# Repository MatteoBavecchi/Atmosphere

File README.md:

# Atmosphere

Air Quality Home Device

## Introduction

Atmosphere is the prototype of a device that detects some values of the surrounding air and let the the user know when it seems not to be livable.

All this is possible with the use of gas sensors, temperature sensors, a buzzer and a WiFi module which sends data collected to two servers.

The goal of the project is create a costomer product, in fact the Atmosphere ecosystem manages more than one user and catalogs the data sent by the various devices in a single database.

Any aspect has been studied to be as much as possible oriented towards an untrained user, and mobile friendly, that is viewable and configurable correctly from any mobile device.

The device is mainly composed by a customized electronic board and a plastic case manufactured with a 3D printer.<br>
Everything has been designed, designed, built and assembled by myself.

## PCB Board Design

I used the Atmega-328p_au for this project.
The PCB board has been made by OSH Park.

<a href="https://oshpark.com/shared_projects/vfo74W1z"></img></a>

## The webserver

Atmosphere communicates with the server http://atmosphere.96.lt and with the Thingspeak server, which can be reached from the IP address 184.106.153.149.
The dialogue with both servers is limited to a GET request on port 80, let's see how:

The syntax of the GET request to the Atmosphere server is as follows:

```
GET /data.php?mac=1&t=2&h=3&gpl=4&co2=5&co=6
```
1: MAC address that resides in the Atmosphere EEPROM.<br>
2: Temperature, expressed in degrees centigrade.<br>
3: Relative humidity, expressed as a percentage.<br>
4: Quantity of LPG in the air, expressed in ppm.<br>
5: Amount of CO2 present in the air, expressed in ppm.<br>
6: Amount of carbon monoxide in the air, expressed in ppm.<br>

The sintax for send data to the Thingspeak server is as follows:

```
GET   /update?key=1&field1=2&field2=3&field3=4&field4=5&field5=6
```
1: Thingspeak private key<br>
2: Temperature, in degrees centigrade.<br>
3: Relative humidity, expressed as a percentage.<br>
4: Quantity of LPG in the air, expressed in ppm.<br>
5: Amount of CO2 present in the air, expressed in ppm.<br>
6: Amount of carbon monoxide in the air, expressed in ppm.<br>

<br><br>
## How the device works

Atmosphere doesn't need expert users to be used, you just need to power on and it will automatically calibrate itself and begin to analyze the surrounding air, sending, every 30 seconds, the data on the internet.
Atmosphere has not any button or display that allows you to configure it. To make it connect to your home WiFi network, I created a smartphone app, which can communicate the login credentials to Atmosphere.

### First Startup
Atmosphere, when powered on, creates a WiFi network, this will be accessible for one minute.
We connect our smartphone to this network and start the "Atmosphere" App.
We have two fields to fill, the name of the network and the password, and under the "Send" button.
Below there's the MAC address of Atmosphere, this must be entered on the website during registration. By doing so, we associate our newly created account with our Atmosphere.
Let's go back to the smartphone and type the network credentials in the fields and press "Send".
Atmosphere will store them inside the EEPROM and connect to the desired network.

It can be powered with a micro usb cable, but even without this, it works for about an hour thanks to the internal battery.

<br><br>
## Database

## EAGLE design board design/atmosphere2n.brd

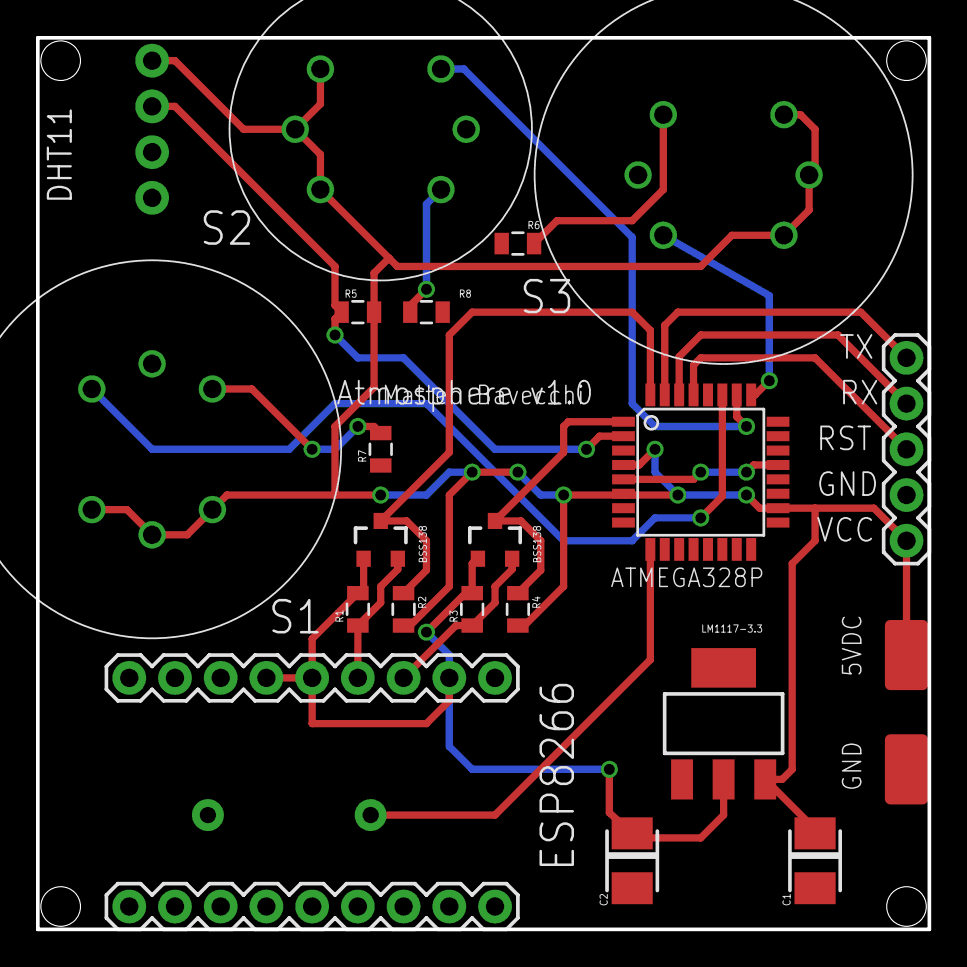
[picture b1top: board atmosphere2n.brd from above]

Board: 2 copper layers, 49.5 x 49.5 mm, 25 parts (0 on the bottom side), 18 nets.

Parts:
+: LUXEON-PAD
-: LUXEON-PAD
ATMEGA328P-AU: ATMEGA328; TQFP32-08
BSS138, BSS138-2: SOT23-3
BUZZER: BUZZERPTH; BUZZER-12MM
C1, C2: 10uF; C3528-21/T
DHT11: 1X04_NO_SILK_ALL_ROUND
ESP-ADC1, ESP-ADC2: 1X09
FRAME1: FRAME-LETTER; CREATIVE_COMMONS
J1: 1X05
MQ-2, MQ-135: METHANE_SENSOR; MQ-3
R1, R2, R3, R4, R5, R6, R7, R8: 0805
U1: SOT223
U$1: METHANE_SENSOR; MQ-3

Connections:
3.3V: BSS138.1, BSS138-2.1, C2.+, ESP-ADC1.2, ESP-ADC1.5, ESP-ADC1.6, R1.2, R3.2, U1.2
5V: +.P$1, ATMEGA328P-AU.4, ATMEGA328P-AU.6, ATMEGA328P-AU.18, C1.+, DHT11.1, J1.1, MQ-2.A1, MQ-2.A2, MQ-2.HA, MQ-135.A1, MQ-135.A2, MQ-135.HA, R2.2, R4.2, R5.2, U1.3, U$1.A1, U$1.A2, U$1.HA
DHT-11: ATMEGA328P-AU.2, DHT11.2, R5.1
ESP_3.3_RX: BSS138-2.2, ESP-ADC1.3, R3.1
ESP_3.3_TX: BSS138.2, ESP-ADC1.4, R1.1
ESP_RX: ATMEGA328P-AU.32, BSS138.3, R2.1
ESP_TX: ATMEGA328P-AU.1, BSS138-2.3, R4.1
GND: -.P$1, ATMEGA328P-AU.3, ATMEGA328P-AU.5, ATMEGA328P-AU.21, BUZZER.-, C1.-, C2.-, DHT11.4, ESP-ADC1.1, J1.2, MQ-2.HB, MQ-135.HB, R6.1, R7.1, R8.2, U1.1, U$1.HB
MQ-2: ATMEGA328P-AU.26, MQ-2.B1
MQ-7: ATMEGA328P-AU.25, U$1.B1
MQ-135: ATMEGA328P-AU.27, MQ-135.B1
unnamed: ATMEGA328P-AU.9, BUZZER.+
unnamed: MQ-2.B2, R8.1
unnamed: MQ-135.B2, R7.2
unnamed: R6.2, U$1.B2
RST: ATMEGA328P-AU.29, J1.3
RX: ATMEGA328P-AU.30, J1.4
TX: ATMEGA328P-AU.31, J1.5

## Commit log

2018-01-22 Create website
2018-01-22 Rename activation.php to website/activation.php
2018-01-22 Rename data.php to website/data.php
2018-01-22 Rename index.php to website/index.php
2018-01-22 Rename login.php to website/login.php
2018-01-22 Rename recover.php to website/recover.php
2018-01-22 Rename registrazione.php to website/registrazione.php
2018-01-22 Create Board design
2018-01-22 Rename Board design to board design/board design
2018-01-22 Create Atmosphere firmware
2018-01-22 Create ciao
2022-06-13 English improvements

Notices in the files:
parts and their libraries:
SparkFun-Connectors: Licensing: Creative Commons ShareAlike 4.0 International - https://creativecommons.org/licenses/by-sa/4.0
SparkFun-Retired: Released under the Creative Commons Attribution Share-Alike 3.0 License
SparkFun-Retired: https://creativecommons.org/licenses/by-sa/3.0
